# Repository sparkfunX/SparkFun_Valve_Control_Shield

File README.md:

SparkFun Dual Valve and Solenoid Control
===========================================================

License Information
-------------------

This product is _**open source**_! 

Various bits of the code have different licenses applied. Anything SparkFun wrote is beerware; if you see me (or any other SparkFun employee) at the local, and you've found our code helpful, please buy us a round!

* Hardware license: CERN 1.2
* Software License: MIT
* Documentation: CC BY-SA 4.0

Please use, reuse, and modify these files as you see fit. Please maintain attribution to SparkFun Electronics and release anything derivative under the same license.

Distributed as-is; no warranty is given.

- Your friends at SparkFun.

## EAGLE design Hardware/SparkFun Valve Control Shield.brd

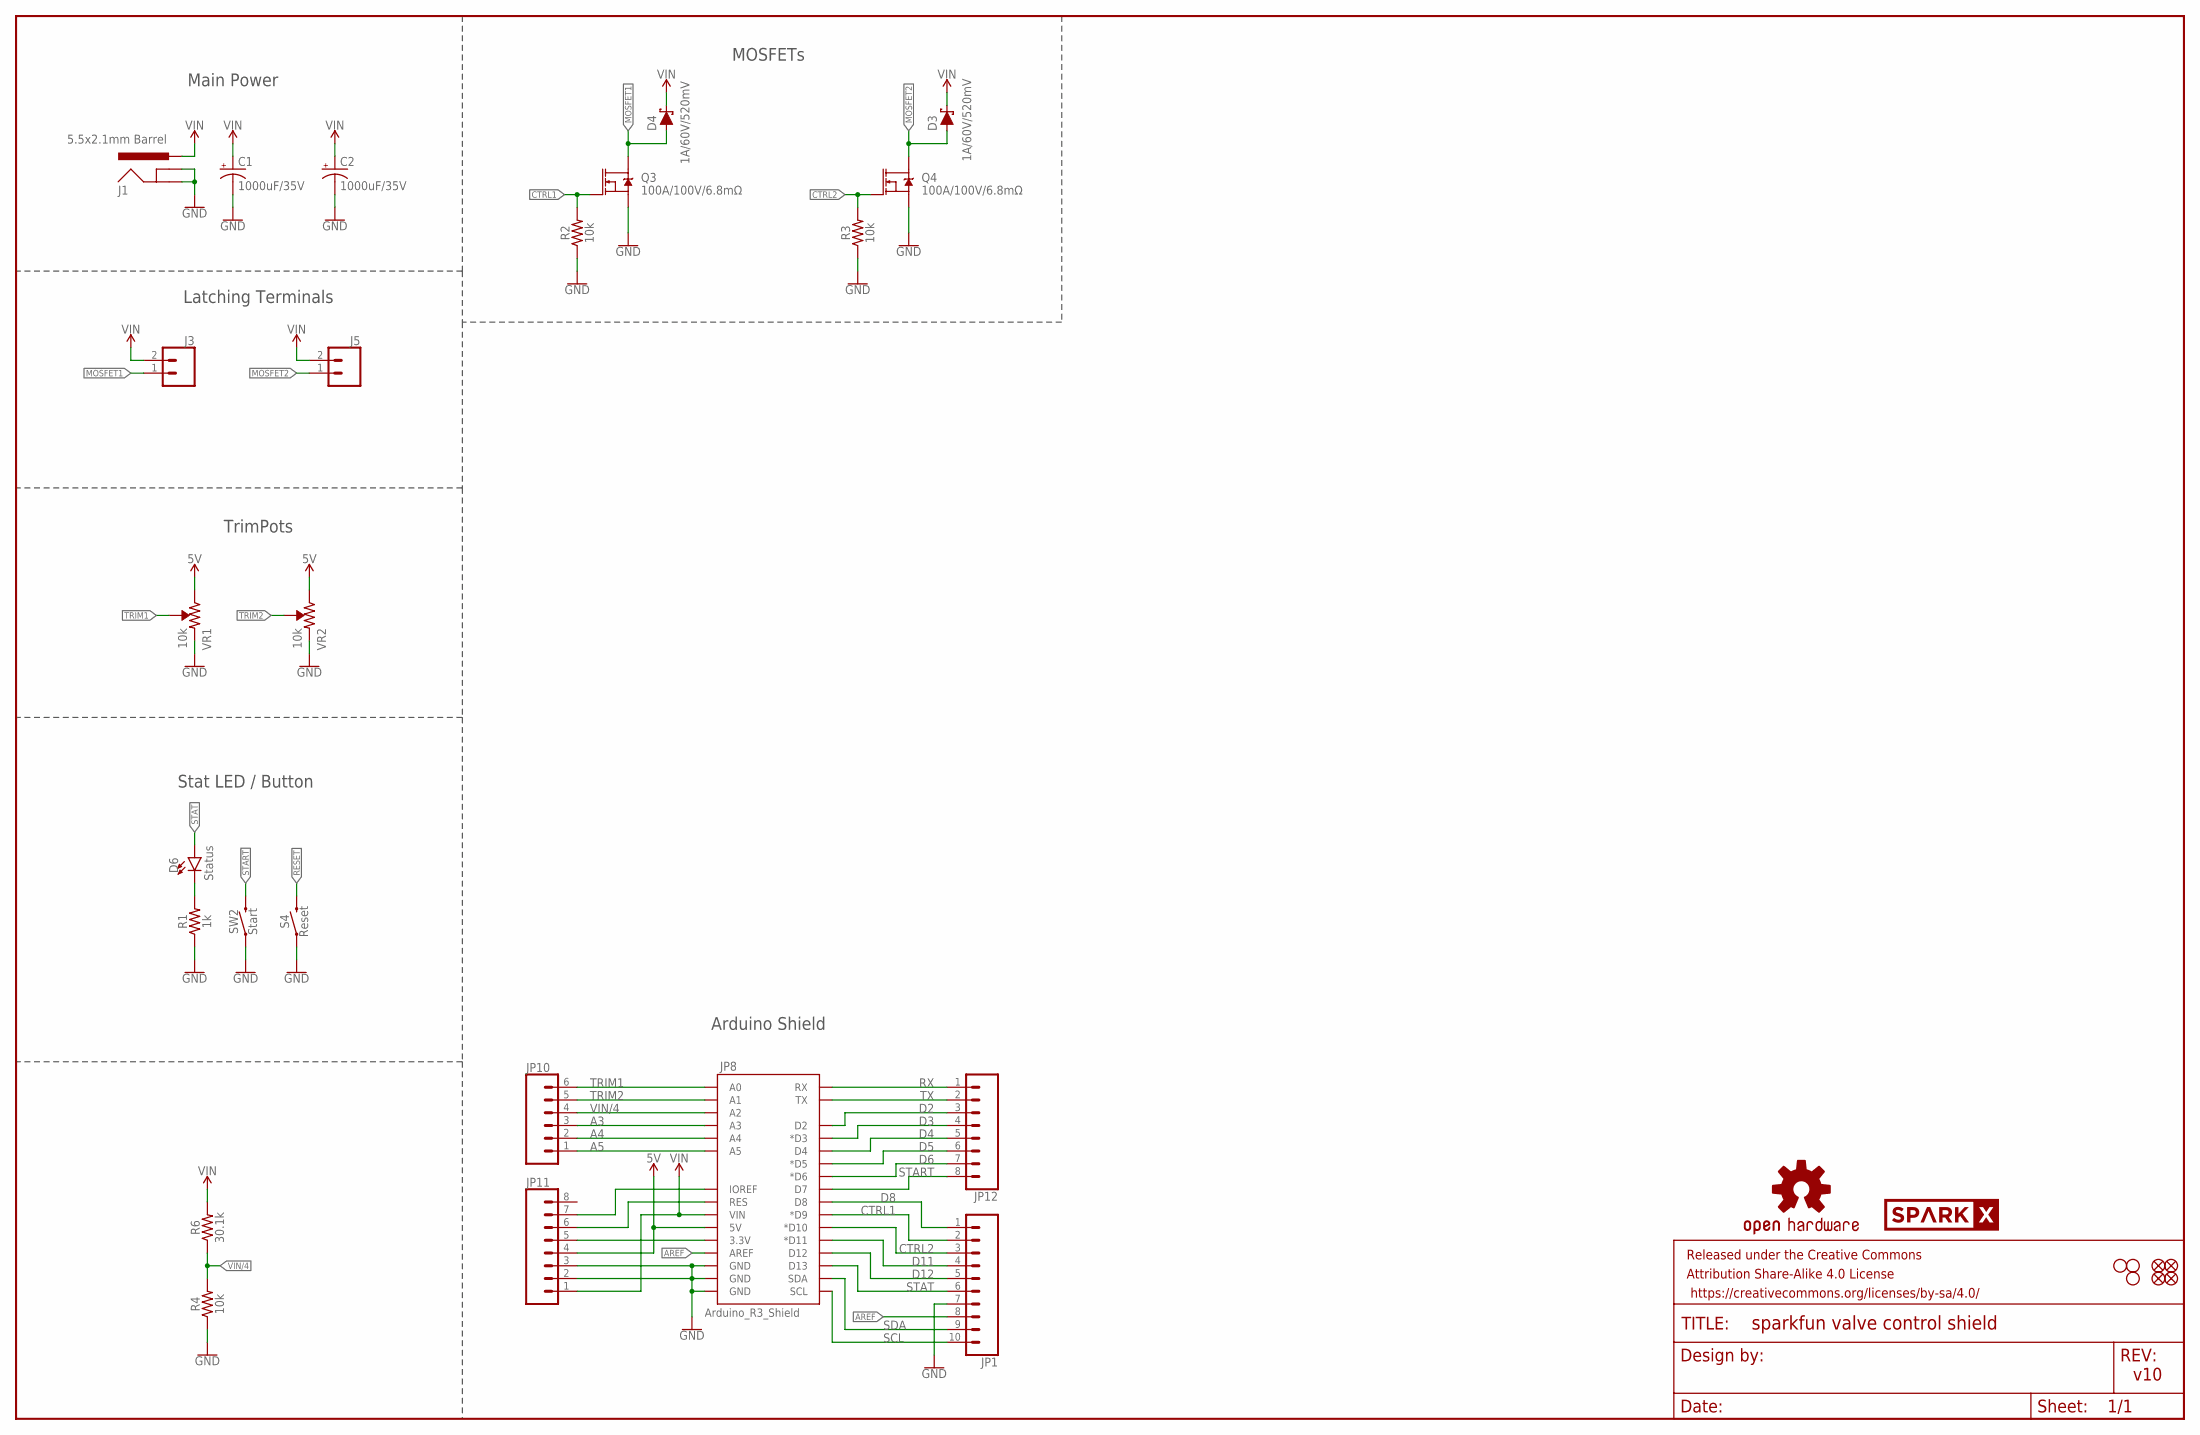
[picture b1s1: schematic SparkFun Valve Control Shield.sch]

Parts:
C1, C2: 1000uF/35V; CPOL-RADIAL-5MM-10MM-KIT
D3, D4: 1A/60V/520mV; DIODE-MICRO-SMP
D6: Status; LED-1206
FD1, FD2, FD3, FD4: FIDUCIAL1X2; FIDUCIAL-1X2
FRAME2: FRAME-LEDGER; CREATIVE_COMMONS
H1, H2, H4: STAND-OFF
J1: 5.5x2.1mm Barrel; POWER_JACK_SMD
J3, J5: CONN_02LATCH_2; LATCHTERMINAL-5MM-2
JP1: CONN_10NO_SILK_PTH_FEMALE; 1X10_NO_SILK
JP8: ARDUINO_R3_SHIELDNOLABELS; UNO_R3_SHIELD_NOLABELS
JP10: CONN_06NO_SILK_NO_POP; 1X06_NO_SILK
JP11, JP12: CONN_08NO_SILK_FEMALE_PTH; 1X08_NO_SILK
LOGO1: OSHW-LOGOS; OSHW-LOGO-S
Q3, Q4: 100A/100V/6.8mΩ; TO-263/D2PAK
R1: 1k; 0603
R2, R3, R4: 10k; 0603
R6: 30.1k; 0603
S4: Reset; TACTILE_SWITCH_SMD_5.2MM
SW2: Start; TACTILE_SWITCH_SMD_5.2MM
U$1: SPARKX-LOGO5; SPARKX-LARGE
VR1, VR2: 10k; TRIMPOT-PTH-3386U

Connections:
3.3: JP8.3.3V, JP11.5
5V: JP8.5V, JP11.4, VR1.3 (CW), VR2.3 (CW)
A3: JP8.A3, JP10.3
A4: JP8.A4, JP10.2
A5: JP8.A5, JP10.1
AREF: JP1.8, JP8.AREF
CTRL1: JP1.2, JP8.D9 (*D9), Q3.1 (G), R2.2
CTRL2: JP1.3, JP8.D10 (*D10), Q4.1 (G), R3.2
D2: JP8.D2, JP12.3
D3: JP8.D3 (*D3), JP12.4
D4: JP8.D4, JP12.5
D5: JP8.D5 (*D5), JP12.6
D6: JP8.D6 (*D6), JP12.7
D8: JP1.1, JP8.D8
D11: JP1.4, JP8.D11 (*D11)
D12: JP1.5, JP8.D12
GND: C1.-, C2.-, J1.GND (GNDBREAK), J1.P$4 (GND), JP1.7, JP8.GND@0 (GND), JP8.GND@1 (GND), JP8.GND@2 (GND), JP11.2, JP11.3, Q3.3 (S), Q4.3 (S), R1.1, R2.1, R3.1, R4.1, S4.1, SW2.1, VR1.1 (CCW), VR2.1 (CCW)
MOSFET1: D4.A, J3.1, Q3.2 (D)
MOSFET2: D3.A, J5.1, Q4.2 (D)
unnamed: JP8.IOREF, JP11.7
unnamed: D6.C, R1.2
RESET: JP8.RES, JP11.6, S4.3 (2)
RX: JP8.RX, JP12.1
SCL: JP1.10, JP8.SCL
SDA: JP1.9, JP8.SDA
START: JP8.D7, JP12.8, SW2.3 (2)
STAT: D6.A, JP1.6, JP8.D13
TRIM1: JP8.A0, JP10.6, VR1.2 (WIPER)
TRIM2: JP8.A1, JP10.5, VR2.2 (WIPER)
TX: JP8.TX, JP12.2
VIN: C1.+, C2.+, D3.C, D4.C, J1.VIN0 (PWR), J3.2, J5.2, JP8.VIN, JP11.1, R6.2
VIN/4: JP8.A2, JP10.4, R4.2, R6.1

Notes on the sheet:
v10
Arduino_R3_Shield
Stat LED / Button
Arduino Shield
MOSFETs
Latching Terminals
Main Power
TrimPots

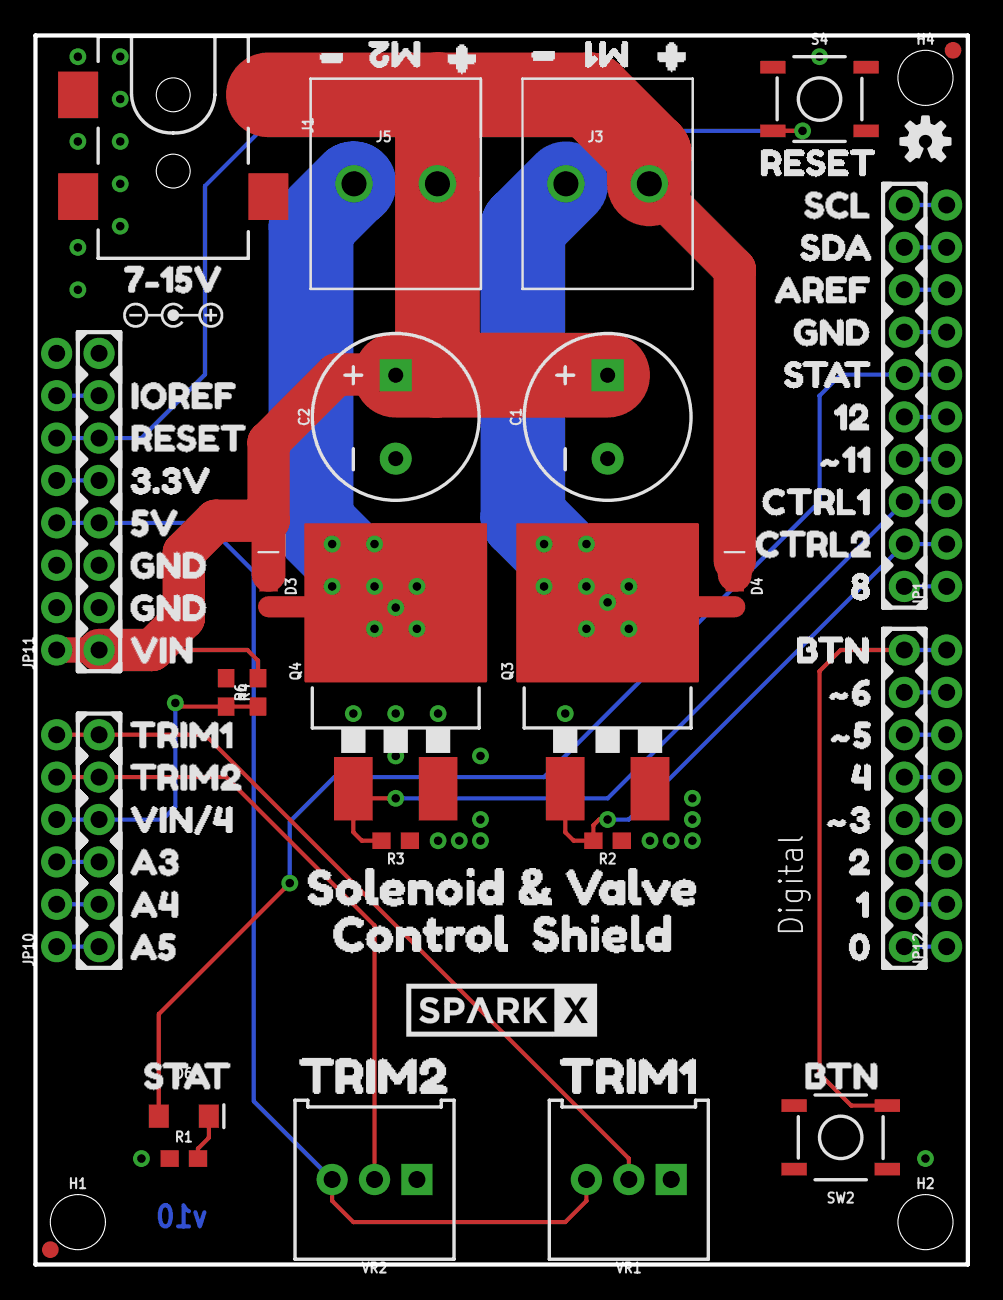
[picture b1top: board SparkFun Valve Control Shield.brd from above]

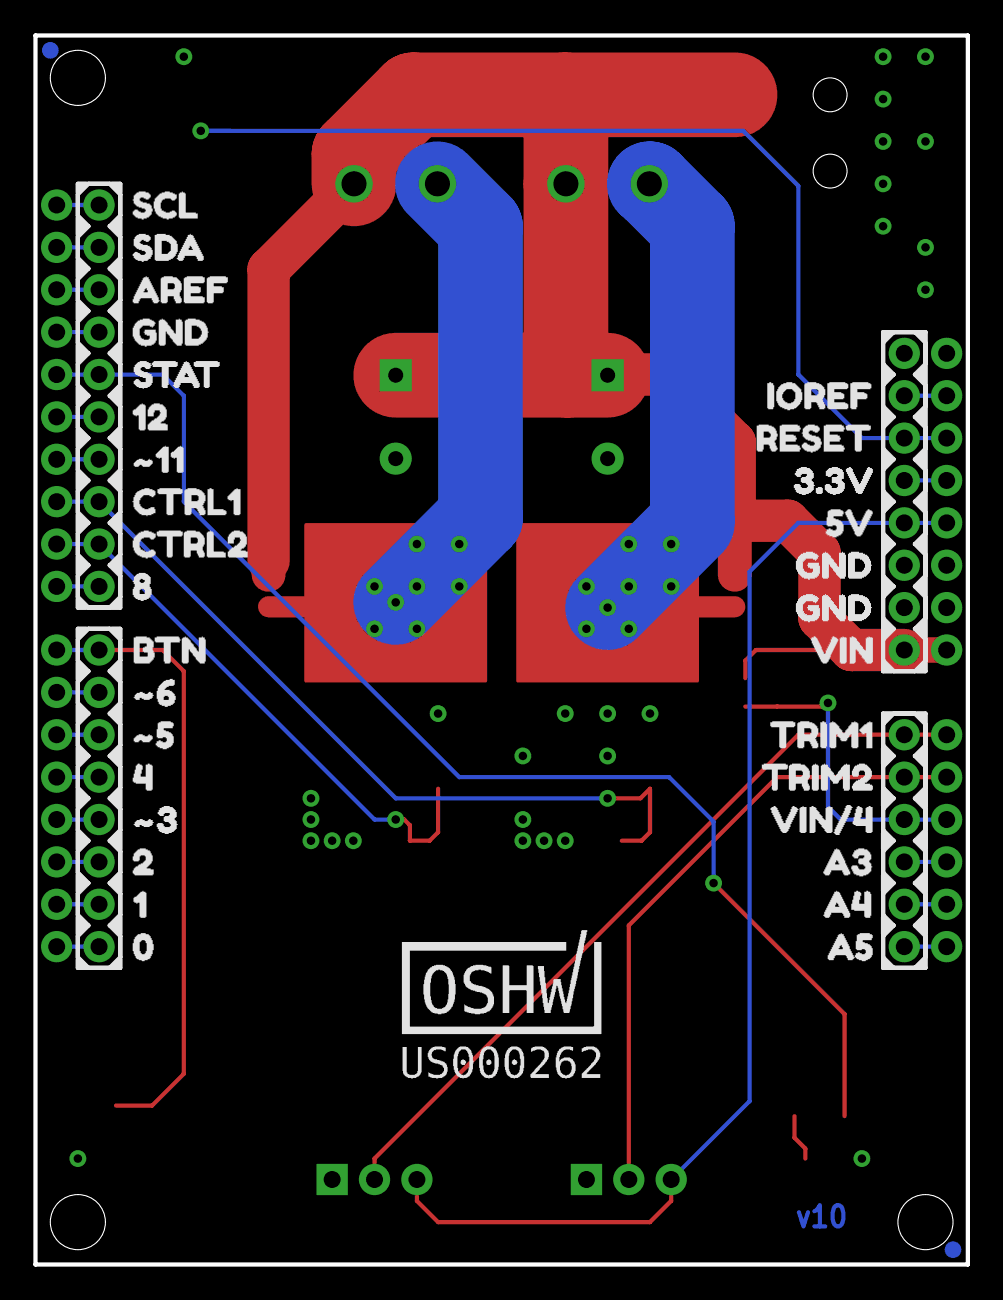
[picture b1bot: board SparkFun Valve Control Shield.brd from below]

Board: 2 copper layers, 55.9 x 73.7 mm, 113 parts (34 on the bottom side), 32 nets.

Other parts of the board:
U$2: RESET1
U$3, U$24: 3#3V8
U$4: POLARITY_MARKING_CENTER_POSITIVE#JPG
U$5, U$72: #58
U$6, U$73: #67
U$7, U$55: VIN0
U$8: 7#15V0
U$9, U$62: #115
U$10, U$74: #314
U$11, U$75: 49
U$12, U$71: 86
U$13, U$76: 116
U$14, U$77: 017
U$15, U$63: 124
U$16, U$78: 215
U$17, U$64: AREF11
U$18, U$65: CTRL12
U$19, U$66: CTRL23
U$20, U$67: GND10
U$21, U$68: SCL13
U$22, U$69: SDA12
U$23, U$35, U$70: STAT1
U$25, U$26: 5V7
U$27, U$80: VIN#40
U$28, U$57: A32
U$29, U$58: A43
U$30, U$59: A54
U$31, U$32, U$49, U$52: GND6
U$33, U$53: IOREF10
U$34, U$54: RESET9
U$36, U$37, U$79: BTN1
U$38: CONTROL2
U$39: SHIELD0
U$40: TRIM10
U$41: SOLENOID_#_VALVE5
U$42, U$60: TRIM12
U$43: TRIM21
U$44, U$61: TRIM23
U$45, U$47: #2
U$46, U$48: #3
U$50: M11
U$51: M22
U$56: OSHW_MARK_US000262#PNG

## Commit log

2020-04-08 Add readme, udpate silk on vin, and add ignore.
2020-04-08 Format readme

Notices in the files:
parts and their libraries:
SparkFun-Aesthetics: Licensing: Creative Commons ShareAlike 4.0 International - https://creativecommons.org/licenses/by-sa/4.0
SparkFun-Aesthetics: Released under the Creative Commons Attribution Share-Alike 4.0 License
SparkFun-Aesthetics: https://creativecommons.org/licenses/by-sa/4.0
